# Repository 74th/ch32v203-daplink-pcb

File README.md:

# CH32V203 を利用した DAPLink

- Shop: https://booth.pm/ja/items/4916891

## features

- SWD のデバッガとして使える
- USB シリアル変換として使える
- 1.27mm ピッチ 10 ピンの SWD と互換性のあるポートを持っている（ただし SWO はなし）
- Arduino UNO R4 の SWD + UART の 1.27mm ピッチ 10 ピンと互換性のあるポートを持っている
- 10 ピンコネクタの VCC を 5V、3.3V を切り替えることができる（Arduino UNO R4 では 5V が必要）
- USB-C

## SWD 10pin Connector

## Firmware

https://github.com/XIVN1987/DAPLink/tree/master/CH32V203

## v1.1.0

R2、R3 は NC にすること。

- semantics: [pdf](ch32v203-daplink-v1.1.0-semantics.pdf) [kicanvas](https://kicanvas.org/?github=https%3A%2F%2Fgithub.com%2F74th%2Fch32v203-daplink-pcb%2Fblob%2Fmain%2Fch32v203-daplink-pcb.kicad_sch)
- pcb: [pdf](ch32v203-daplink-v1.1.0-pcb.pdf) [kicanvas](https://kicanvas.org/?github=https%3A%2F%2Fgithub.com%2F74th%2Fch32v203-daplink-pcb%2Fblob%2Fmain%2Fch32v203-daplink-pcb.kicad_pcb)

## BOM

| Reference  | Name                               | Quantity |
| ---------- | ---------------------------------- | -------- |
| C1, C2     | Capacitor 0603 22pF                | 2        |
| C3, C4, C7 | Capacitor 0603 10uF                | 3        |
| C5         | Capacitor 0603 2.2uF               | 1        |
| C6, C8, C9 | Capacitor 0603 100nF               | 3        |
| D1         | LED 0805 Blue                      | 1        |
| D2         | LED 0805 Red                       | 1        |
| J1         | USB Type-C Receptacle              | 1        |
| J2         | Box Pin Header 2x5 Pitch 1.27mm    | 1        |
| J3         | Pin Header 2x5 Pitch 2.54mm        | 1        |
| R1, R5     | Register 0603 10kΩ                 | 2        |
| R2, R3     | NC                                 | 2        |
| R4, R6, R7 | Register 0603 5.1kΩ                | 3        |
| SW1        | Slide Switch                       | 1        |
| U1         | MCU LQFP48 WCH CH32V203C8T6        | 1        |
| U2         | Regulator 3.3V SOT-223 AMS1117-3.3 | 1        |
| Y1         | Crystal 3225 8MHz                  | 1        |

## LICENSE

- Firmware: https://github.com/XIVN1987/DAPLink/blob/master/LICENSE
- PCB: MIT

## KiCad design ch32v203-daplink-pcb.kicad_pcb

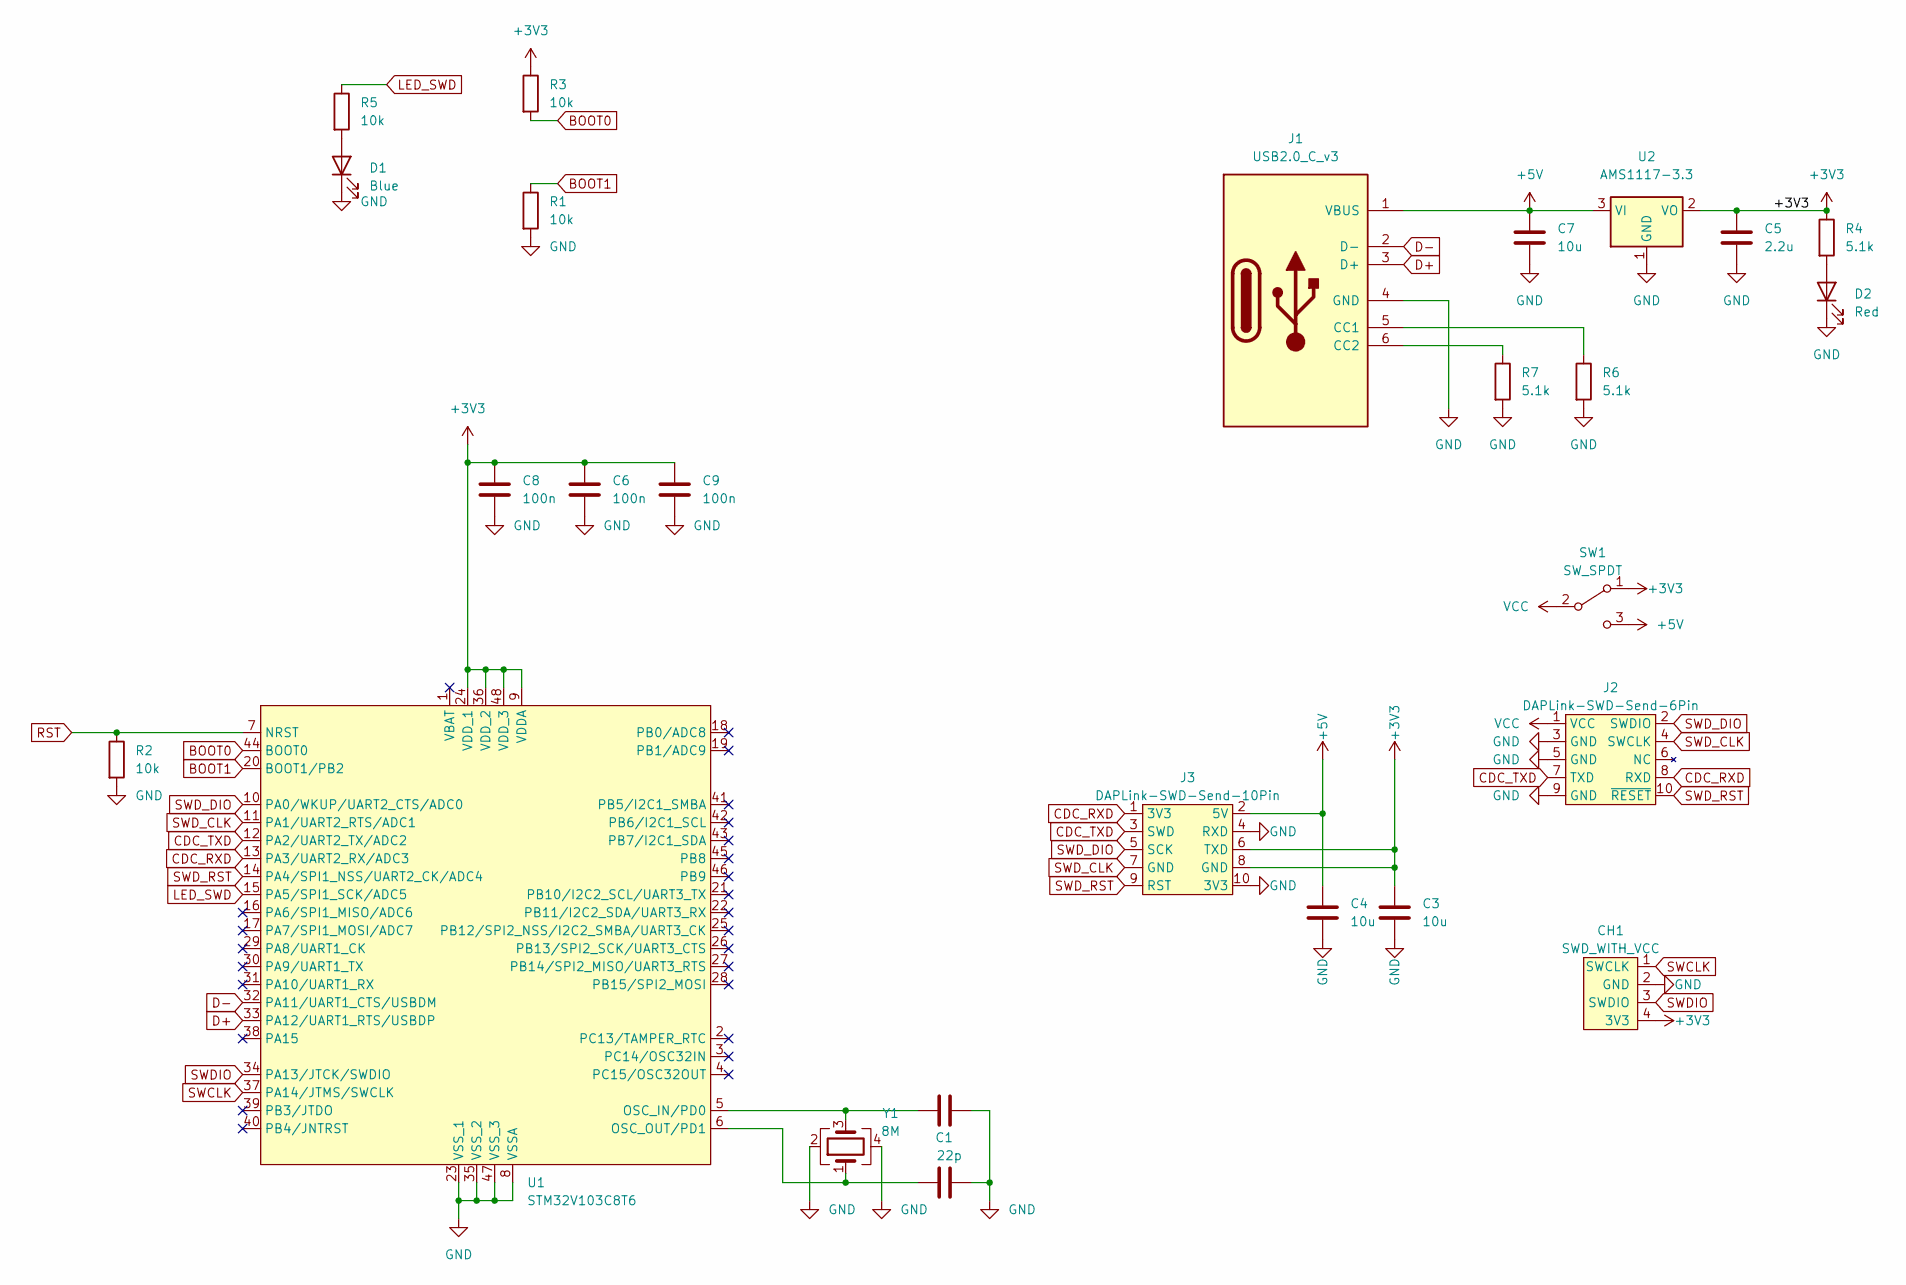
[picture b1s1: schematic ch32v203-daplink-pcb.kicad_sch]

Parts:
C1, C2: 22p; Capacitor_0603_1608
C3, C4, C7: 10u; Capacitor_0603_1608
C5: 2.2u; Capacitor_0603_1608
C6, C8, C9: 100n; Capacitor_0603_1608
CH1: SWD_WITH_VCC; SWD-4Pin
D1: Blue; LED_0805_2012Metric_Pad1.15x1.40mm_HandSolder
D2: Red; LED_0805_2012Metric_Pad1.15x1.40mm_HandSolder
J1: USB2.0_C_v3; USB-C-12-Pin-SMD
J2: DAPLink-SWD-Send-6Pin; BoxPinHeader_2x05_P1.27mm_Vertical
J3: DAPLink-SWD-Send-10Pin; Side-2x5P-PinHeader-Right
R1, R2, R3, R5: 10k; Register_0603_1608
R4, R6, R7: 5.1k; Register_0603_1608
SW1: SW_SPDT; Slide_Switch
U1: STM32V103C8T6; LQFP-48_7x7mm_P0.5mm
U2: AMS1117-3.3; SOT-223-3_TabPin2
Y1: 8M; Crystal_SMD_3225-4Pin_3.2x2.5mm_HandSoldering

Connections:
+3V3: C3.1, C5.1, C6.1, C8.1, C9.1, CH1.4 (3V3), J3.6 (TXD), J3.8 (GND), R3.1, R4.1, SW1.1 (A), U1.9 (VDDA), U1.24 (VDD_1), U1.36 (VDD_2), U1.48 (VDD_3), U2.2 (VO)
+5V: C4.1, C7.1, J1.1 (VBUS), J3.2 (5V), SW1.3 (C), U2.3 (VI)
BOOT0: R3.2, U1.44 (BOOT0)
BOOT1: R1.1, U1.20 (BOOT1/PB2)
CDC_RXD: J2.8 (RXD), J3.1 (3V3), U1.13 (PA3/UART2_RX/ADC3)
CDC_TXD: J2.7 (TXD), J3.3 (SWD), U1.12 (PA2/UART2_TX/ADC2)
D+: J1.3 (D+), U1.33 (PA12/UART1_RTS/USBDP)
D-: J1.2 (D-), U1.32 (PA11/UART1_CTS/USBDM)
GND: C1.2, C2.2, C3.2, C4.2, C5.2, C6.2, C7.2, C8.2, C9.2, CH1.2 (GND), D1.1 (K), D2.1 (K), J1.4 (GND), J2.3 (GND), J2.5 (GND), J2.9 (GND), J3.4 (RXD), J3.10 (3V3), R1.2, R2.2, R6.2, R7.2, U1.8 (VSSA), U1.23 (VSS_1), U1.35 (VSS_2), U1.47 (VSS_3), U2.1 (GND), Y1.2, Y1.4
LED_SWD: R5.1, U1.15 (PA5/SPI1_SCK/ADC5)
unnamed: D2.2 (A), R4.2
unnamed: D1.2 (A), R5.2
unnamed: J1.5 (CC1), R6.1
unnamed: J1.6 (CC2), R7.1
unnamed: C2.1, U1.5 (OSC_IN/PD0), Y1.3
unnamed: C1.1, U1.6 (OSC_OUT/PD1), Y1.1
RST: R2.1, U1.7 (NRST)
SWCLK: CH1.1 (SWCLK), U1.37 (PA14/JTMS/SWCLK)
SWDIO: CH1.3 (SWDIO), U1.34 (PA13/JTCK/SWDIO)
SWD_CLK: J2.4 (SWCLK), J3.7 (GND), U1.11 (PA1/UART2_RTS/ADC1)
SWD_DIO: J2.2 (SWDIO), J3.5 (SCK), U1.10 (PA0/WKUP/UART2_CTS/ADC0)
SWD_RST: J2.10 (~RESET), J3.9 (RST), U1.14 (PA4/SPI1_NSS/UART2_CK/ADC4)
VCC: J2.1 (VCC), SW1.2 (B)

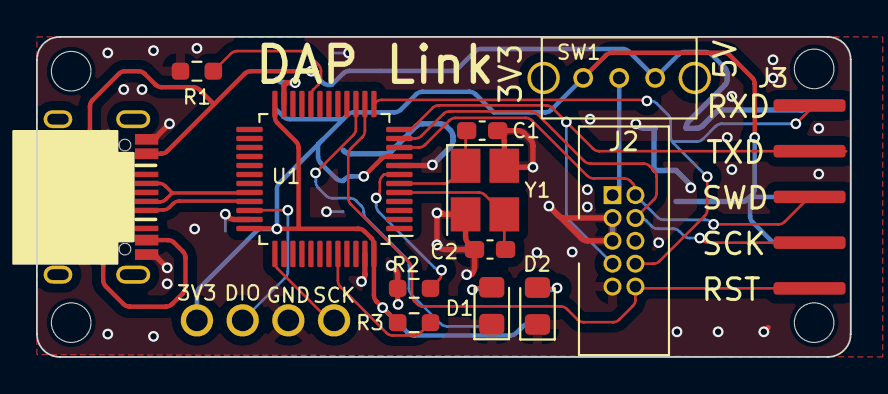
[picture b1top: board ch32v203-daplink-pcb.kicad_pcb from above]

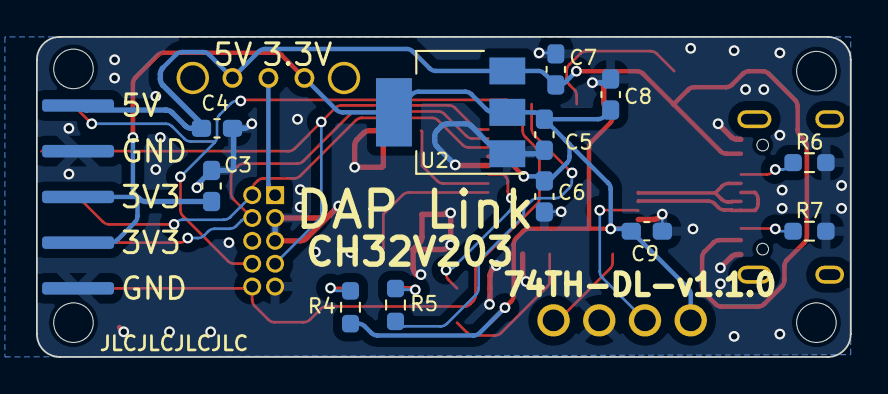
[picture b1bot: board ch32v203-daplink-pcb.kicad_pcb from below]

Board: 2 copper layers, 45.2 x 17.8 mm, 30 parts (12 on the bottom side), 23 nets.

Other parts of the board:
M1, M2, M3, M4: M2-Hole

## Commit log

2023-04-20 Add files via upload
    https://github.com/XIVN1987/DAPLink
2023-04-20 v1.0.0
2023-06-28 for Arduino UNO R4
2023-06-29 v1.1.0
2023-07-08 add pdf
2023-09-02 fix semantics
